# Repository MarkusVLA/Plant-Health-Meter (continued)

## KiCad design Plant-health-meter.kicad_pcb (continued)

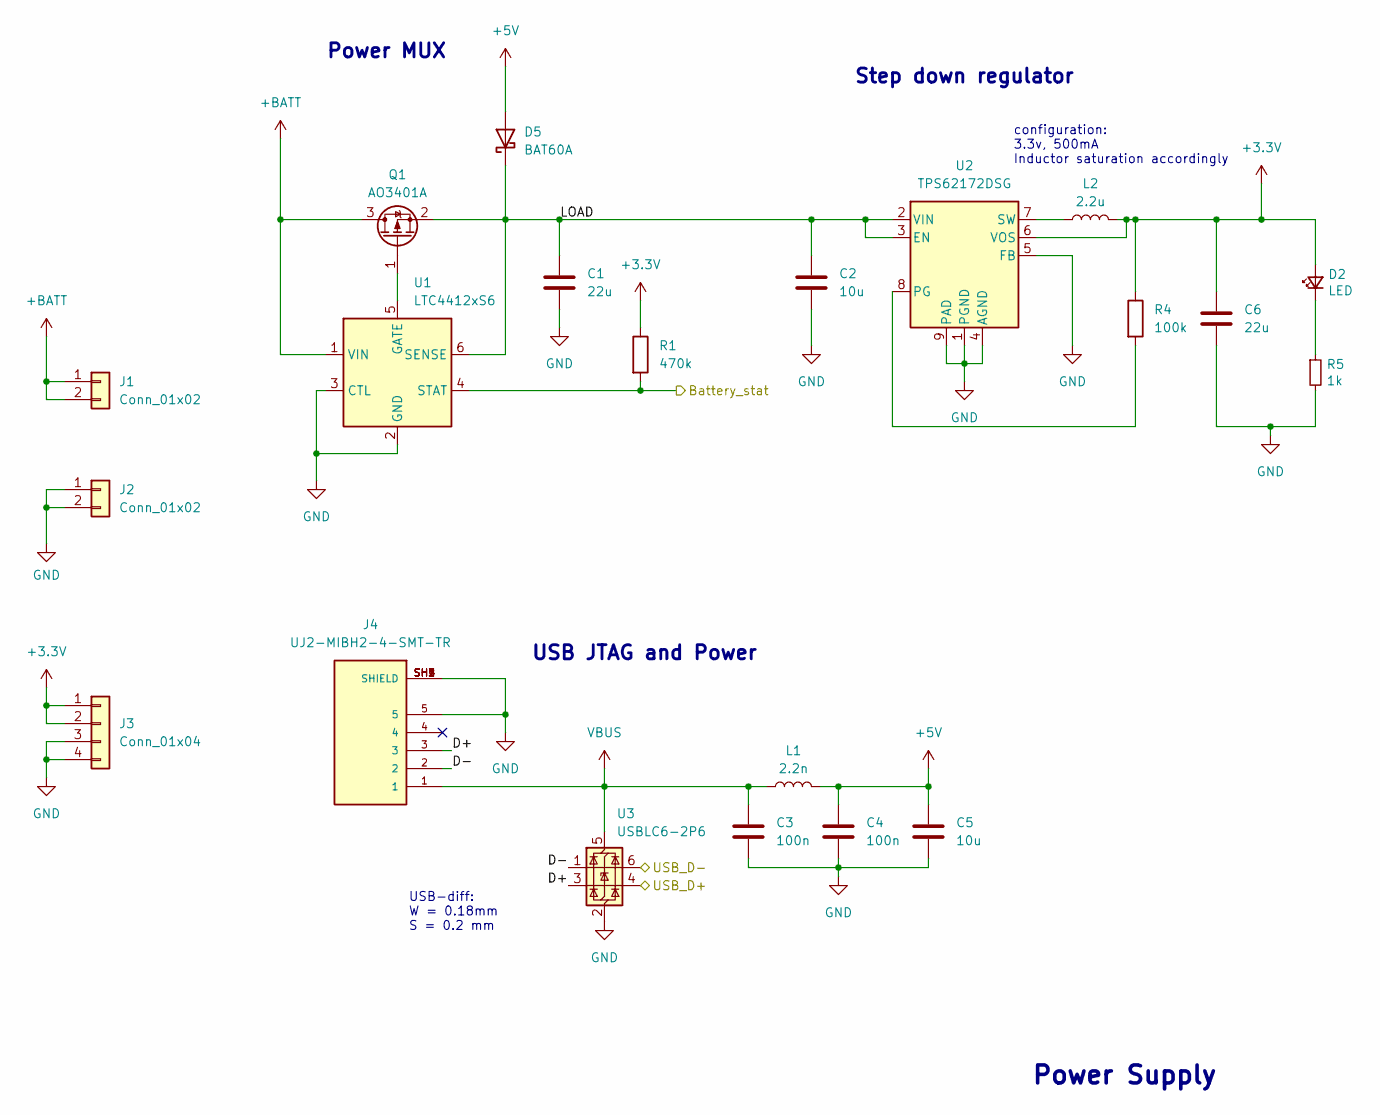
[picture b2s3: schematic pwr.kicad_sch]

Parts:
C1, C6: 22u; C_0805_2012Metric
C2, C5: 10u; C_0603_1608Metric
C3, C4: 100n; C_0402_1005Metric
D2: LED; LED_0805_2012Metric_Pad1.15x1.40mm_HandSolder; LCSC C205445
D5: BAT60A; D_SOD-323
J1, J2: Conn_01x02; PinHeader_1x02_P2.54mm_Vertical
J3: Conn_01x04; PinHeader_1x04_P2.54mm_Vertical
J4: UJ2-MIBH2-4-SMT-TR; CUI_UJ2-MIBH2-4-SMT-TR; PARTREV 1.0
L1: 2.2n; L_0603_1608Metric
L2: 2.2u; L_0805_2012Metric
Q1: AO3401A; SOT-23
R1: 470k; R_0402_1005Metric
R4: 100k; R_0402_1005Metric
R5: 1k; R_0402_1005Metric; LCSC C163928
U1: LTC4412xS6; TSOT-23-6
U2: TPS62172DSG; WSON-8-1EP_2x2mm_P0.5mm_EP0.9x1.6mm_ThermalVias
U3: USBLC6-2P6; SOT-666

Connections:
+3.3V: C6.1, D2.2 (A), J3.1, J3.2, L2.2, R1.1, R4.1, U2.6 (VOS); also elsewhere on the board
+5V: C4.1, C5.1, D5.2 (A), L1.2; also elsewhere on the board
+BATT: J1.1, J1.2, Q1.3 (D), U1.1 (VIN)
/MCU/Battery_stat: R1.2, U1.4 (STAT); also elsewhere on the board
/MCU/USB_D+: U3.4 (I/O2); also elsewhere on the board
/MCU/USB_D-: U3.6 (I/O1); also elsewhere on the board
/PWR/D+: J4.3, U3.3 (I/O2)
/PWR/D-: J4.2, U3.1 (I/O1)
/PWR/LOAD: C1.1, C2.1, D5.1 (K), Q1.2 (S), U1.6 (SENSE), U2.2 (VIN), U2.3 (EN)
GND: C1.2, C2.2, C3.2, C4.2, C5.2, C6.2, J2.1, J2.2, J3.3, J3.4, J4.5, J4.SH1 (SHIELD), J4.SH2 (SHIELD), J4.SH3 (SHIELD), J4.SH4 (SHIELD), J4.SH5 (SHIELD), R5.2, U1.2 (GND), U1.3 (CTL), U2.1 (PGND), U2.4 (AGND), U2.5 (FB), U2.9 (PAD), U3.2 (GND); also elsewhere on the board
unnamed: D2.1 (K), R5.1
unnamed: Q1.1 (G), U1.5 (GATE)
unnamed: R4.2, U2.8 (PG)
unnamed: L2.1, U2.7 (SW)
VBUS: C3.1, J4.1, L1.1, U3.5 (VBUS)

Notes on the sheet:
configuration: 3.3v, 500mA Inductor saturation accordingly
Power MUX
USB JTAG and Power
USB-diff: W = 0.18mm S = 0.2 mm
Step down regulator
Power Supply

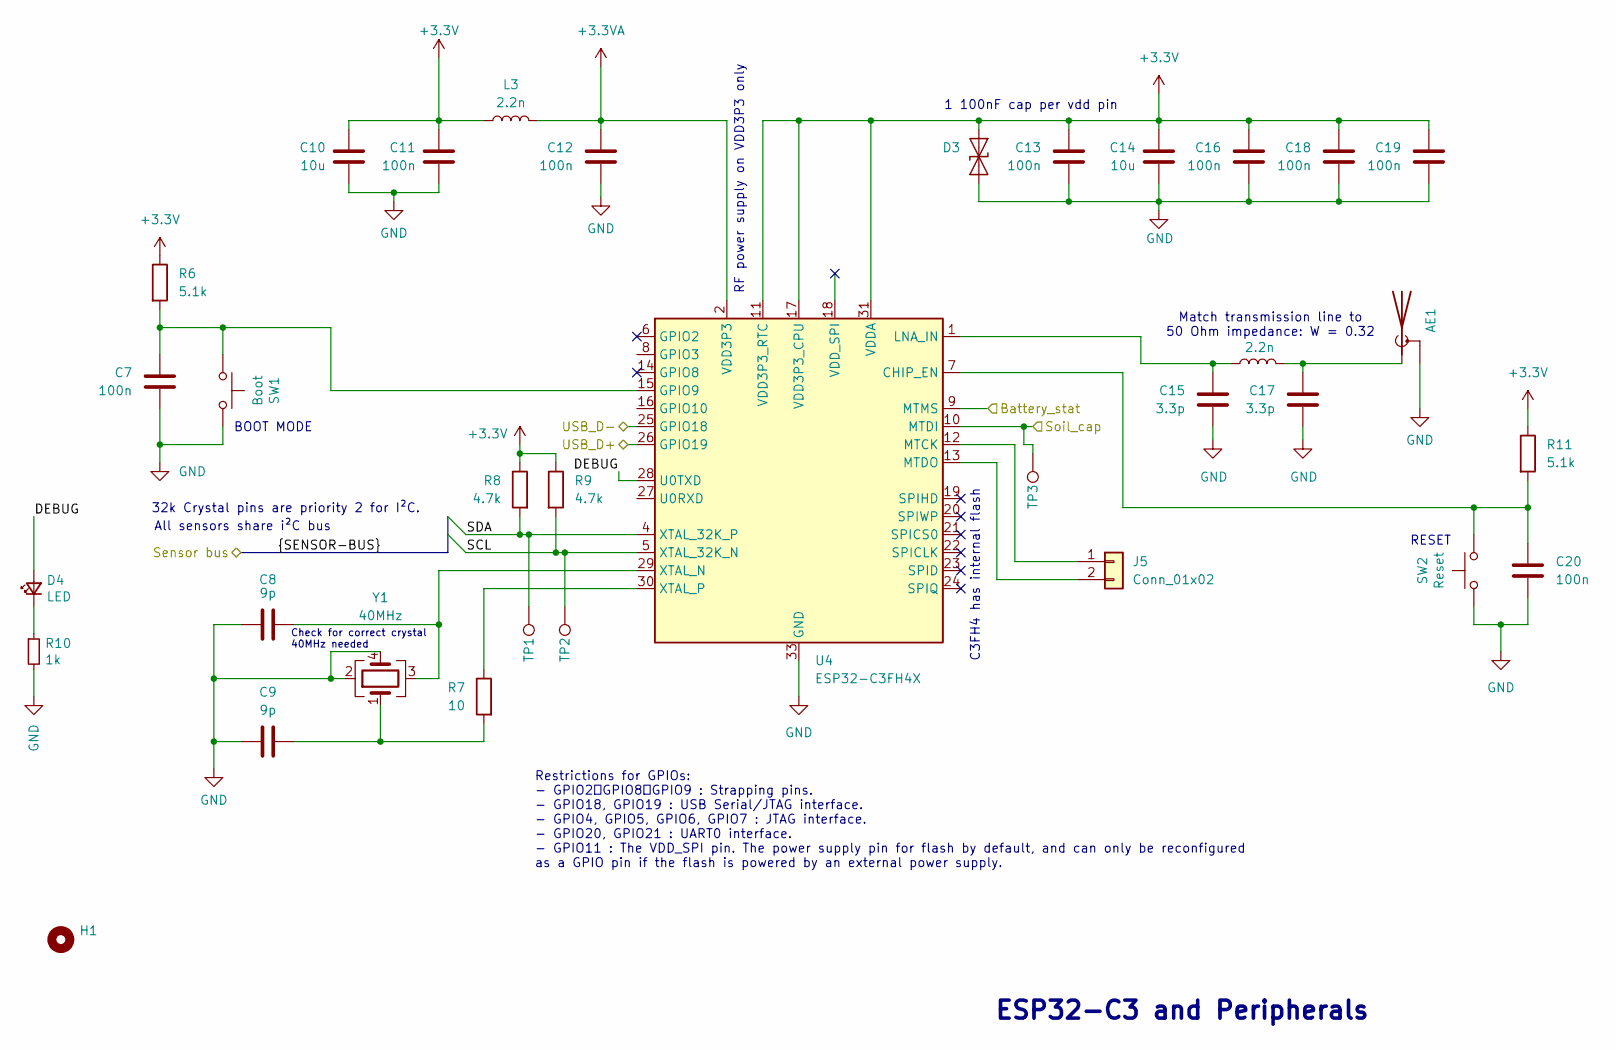
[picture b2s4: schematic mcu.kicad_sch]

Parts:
AE1: Antenna_Shield; Texas_SWRA117D_2.4GHz_Right
C7, C11, C12, C13, C16, C18, C19, C20: 100n; C_0402_1005Metric
C8, C9: 9p; C_0402_1005Metric
C10, C14: 10u; C_0603_1608Metric
C15, C17: 3.3p; C_0402_1005Metric
D3: SZESD9B5.0ST5G; D_SOD-923
D4: LED; LED_0805_2012Metric_Pad1.15x1.40mm_HandSolder; LCSC C205445
H1: MountingHole; MountingHole_2.2mm_M2_DIN965_Pad
J5: Conn_01x02; PinHeader_1x02_P2.54mm_Vertical
L3, L4: 2.2n; L_0402_1005Metric
R6, R11: 5.1k; R_0402_1005Metric
R7: 10; R_0402_1005Metric
R8, R9: 4.7k; R_0402_1005Metric
R10: 1k; R_0402_1005Metric; LCSC C163928
SW1: Boot; SW_Push_SPST_NO_Alps_SKRK; LCSC C115357
SW2: Reset; SW_Push_SPST_NO_Alps_SKRK; LCSC C115357
TP1, TP2, TP3: TestPoint; TestPoint_Pad_D1.0mm
U4: ESP32-C3FH4X; QFN-32-1EP_5x5mm_P0.5mm_EP3.7x3.7mm
Y1: 40MHz; Crystal_SMD_3225-4Pin_3.2x2.5mm

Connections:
+3.3V: C10.1, C11.1, C13.1, C14.1, C16.1, C18.1, C19.1, D3.2 (A2), L3.2, R6.1, R8.1, R9.1, R11.1, U4.11 (VDD3P3_RTC), U4.17 (VDD3P3_CPU), U4.31 (VDDA), U4.32 (VDDA); also elsewhere on the board
+3.3VA: C12.1, L3.1, U4.2 (VDD3P3), U4.3 (VDD3P3)
/MCU/Battery_stat: U4.9 (MTMS); also elsewhere on the board
/MCU/DEBUG: D4.2 (A), U4.28 (U0TXD)
/MCU/SCL: R9.2, TP2.1, U4.5 (XTAL_32K_N); also elsewhere on the board
/MCU/SDA: R8.2, TP1.1, U4.4 (XTAL_32K_P); also elsewhere on the board
/MCU/Soil_cap: TP3.1, U4.10 (MTDI); also elsewhere on the board
/MCU/USB_D+: U4.26 (GPIO19); also elsewhere on the board
/MCU/USB_D-: U4.25 (GPIO18); also elsewhere on the board
GND: AE1.2 (Shield), C7.1, C8.1, C9.1, C10.2, C11.2, C12.2, C13.2, C14.2, C15.2, C16.2, C17.2, C18.2, C19.2, C20.2, D3.1 (A1), R10.2, SW1.2, SW2.2, U4.33 (GND), Y1.2, Y1.4; also elsewhere on the board
unnamed: AE1.1 (A), C17.1, L4.1
unnamed: C9.2, R7.2, Y1.1
unnamed: D4.1 (K), R10.1
unnamed: J5.1, U4.12 (MTCK)
unnamed: J5.2, U4.13 (MTDO)
unnamed: C20.1, R11.2, SW2.1, U4.7 (CHIP_EN)
unnamed: C7.2, R6.2, SW1.1, U4.15 (GPIO9)
unnamed: C15.1, L4.2, U4.1 (LNA_IN)
unnamed: C8.2, U4.29 (XTAL_N), Y1.3
unnamed: R7.1, U4.30 (XTAL_P)

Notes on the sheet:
Match transmission line to 50 Ohm impedance: W = 0.32
32k Crystal pins are priority 2 for I²C.
RESET
ESP32-C3 and Peripherals
BOOT MODE
RF power supply on VDD3P3 only
C3FH4 has internal flash
All sensors share i²C bus
Check for correct crystal 40MHz needed
1 100nF cap per vdd pin
Restrictions for GPIOs: - GPIO2、GPIO8、GPIO9 : Strapping pins. - GPIO18, GPIO19 : USB Serial/JTAG interface. - GPIO4, GPIO5, GPIO6, GPIO7 : JTAG interface. - GPIO20, GPIO21 : UART0 interface. - GPIO11 : The VDD_SPI pin. The power supply pin for flash by default, and can only be reconfigured as a GPI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

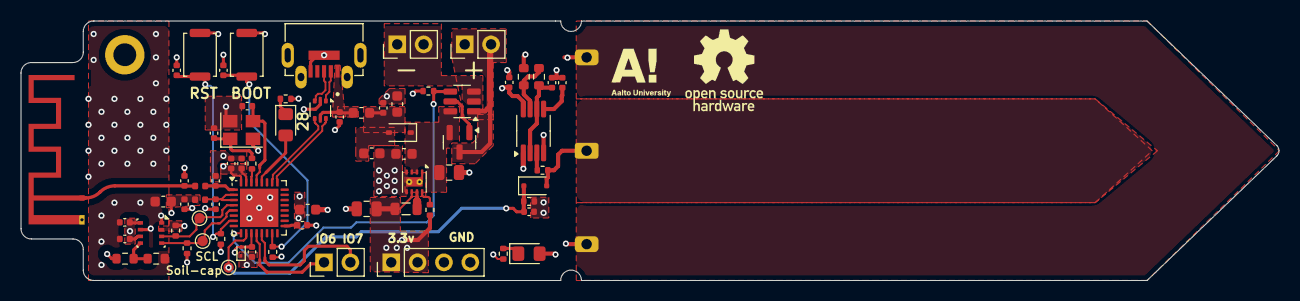
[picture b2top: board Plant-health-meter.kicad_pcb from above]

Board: 4 copper layers, 121.2 x 25.0 mm, 72 parts (0 on the bottom side), 36 nets.

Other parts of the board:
C5#2: 10u; C_0603_1608Metric

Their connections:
+5V: C5#2.1; also elsewhere on the board
GND: C5#2.2; also elsewhere on the board

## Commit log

2025-01-13 Adding files to remote
2025-01-13 Added README file.
2025-01-15 Some updates
2025-01-16 More updates
2025-01-16 Reorganized and added simulation
2025-01-16 Cleaned up
2025-01-16 Removed .DS_Store file
2025-01-17 Set up esp-idf with platformio
2025-01-17 fixed
2025-01-18 Added battery charging circuit and created WiFi api in firmware + created simple server for esp to send data to
2025-01-19 Switched to ESP-idf
2025-01-19 Cleaned firmaware dir
2025-01-19 Removed cache from git
2025-01-19 Improvements and Neovim works correctly now
2025-01-19 Added io config to main: flash led when transmitting data
2025-01-23 Updated some component packages
2025-01-24 created private config for personal information
2025-01-30 added simple REST API for sensor data
2025-02-04 Added light sensor simulation and schematic
2025-02-07 Light sensor
2025-02-13 Removed image
2025-02-13 removed usb port library
2025-02-14 latest
2025-03-09 Optimized PCB lauout and added Header for LED indicator bar
2025-03-09 Modified .gitignore
2025-03-09 Finished PCB routing and added reference designators
2025-03-09 removed unused file
2025-03-09 Added link to esp programming guide
2025-03-10 Corrected link to C3
2025-03-11 Final touches to PCB
2025-03-11 README update
2025-03-13 ESD protection and Boost UVLO
2025-03-14 Production files
2025-03-18 i2c test code and register definitions for bme280
2025-03-18 Added sdkconfig to .gitignore
2025-03-18 FreeRTOS tasks and deep sleep test
2025-03-18 Fixed spelling mistake
2025-03-19 Added JSON network packet
2025-03-19 more i2c driver code
2025-03-19 moved ADS1115 reg defs file
2025-03-24 Changed packet to use floats for sensor data
2025-03-28 Set configs and pins for c3
2025-04-01 Add firebase rtdb test code
2025-04-01 Add timestamp syncing over ntp
2025-04-02 Add measurements data packet to the firebase put method
2025-04-03 added driver for ADS1115
2025-04-03 Fix warnings in time sync
2025-04-03 Soil moisture working =)
2025-04-03 Add BLE initial setup
2025-04-03 Added support to set wifi password over BLE!
2025-04-04 Change password change flow
2025-04-04 Update readme device setup instructions
2025-04-04 Add LED blinking while BLE is active
2025-04-04 Add device id parameter
2025-04-04 Update setup readme
2025-04-06 Calibrated all sensors
2025-04-06 Added soil moisture sensor polynomial regression script
2025-04-06 Added documatation folder with linear regression model plot
2025-04-10 Added Option to use hard coded wifi credentials
2025-04-18 Create LICENSE
